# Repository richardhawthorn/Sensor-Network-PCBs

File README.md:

# PCBs for a wireless sensor network

- Arduino based
- 3.3V operation
- RMF12B/RFM69W communication

### License

This work is licensed under a Creative Commons Attribution-ShareAlike 4.0 International License.

<br />
Designed by <a xmlns:cc="http://creativecommons.org/ns#" href="http://www.richardhawthorn.com" property="cc:attributionName" rel="cc:attributionURL" target="_blank">Richard Hawthorn</a><br />
<a rel="license" href="http://creativecommons.org/licenses/by-sa/4.0/" target="_blank">View License</a>

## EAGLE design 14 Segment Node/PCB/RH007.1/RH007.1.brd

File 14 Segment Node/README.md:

### Description

14 Segment LED display, powered by Arduino, with a built in RF radio tranceiver.  
The board can be populated as a full Arduino, or as a shield by populating the 14 segment LEDs + driver.

### Features

- 0.54" 14 segment display, 4 character
- HT16K33 i2c LED driver
- ATMEGA328P with Arduino boot-loader
- RMF12B/RFM69W radio
- 3.3V operation
- Mini USB power connector
- FTDI programming port
- ICSP port
- LED output

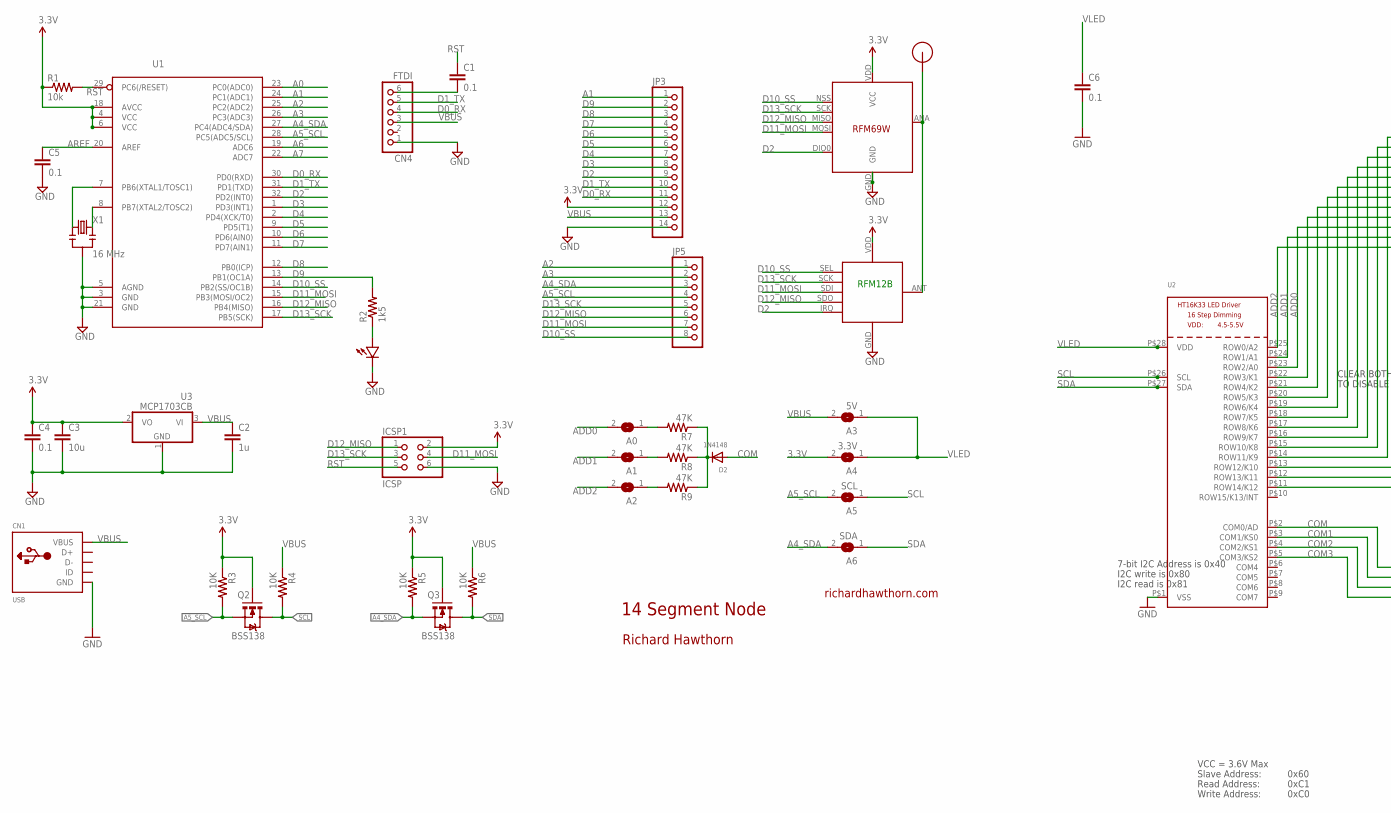
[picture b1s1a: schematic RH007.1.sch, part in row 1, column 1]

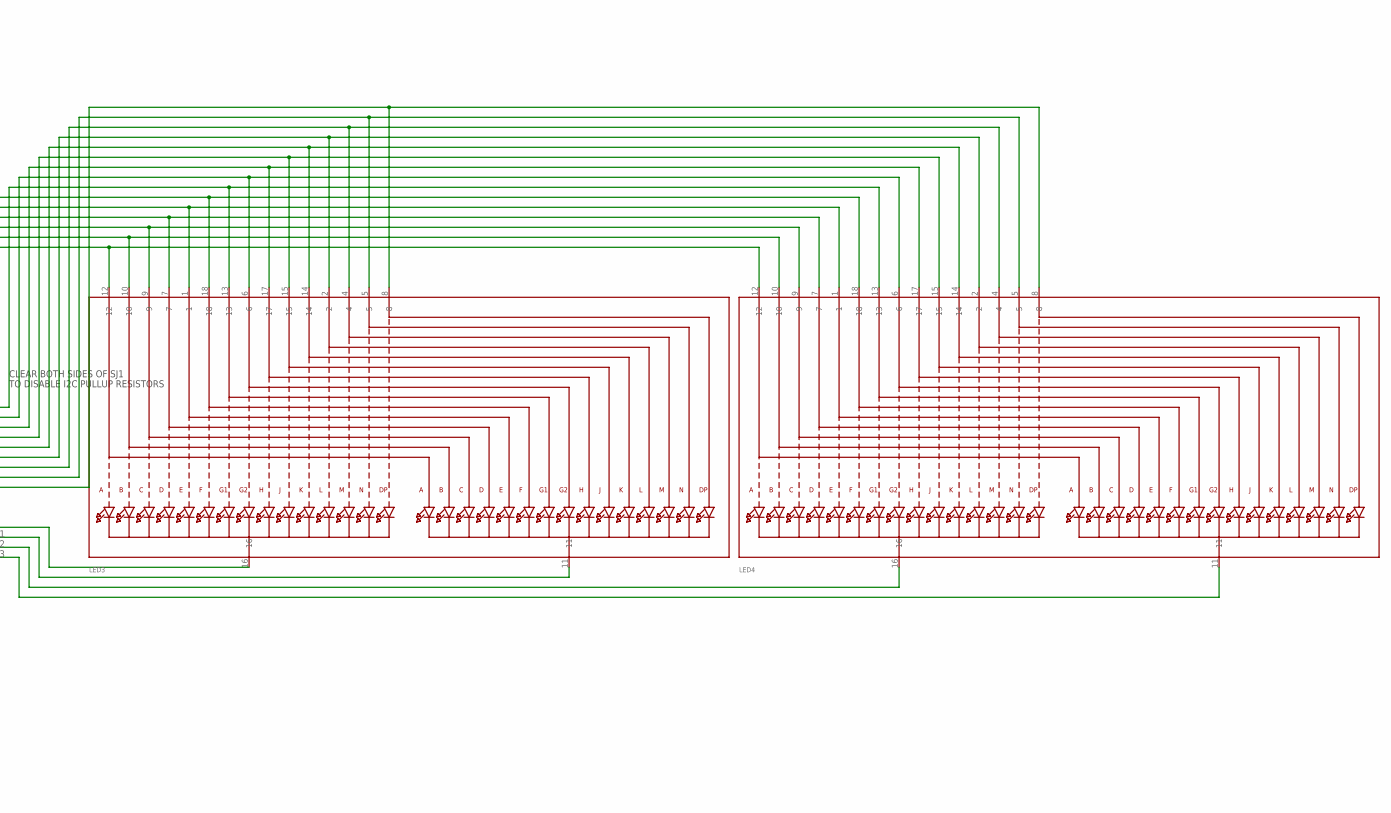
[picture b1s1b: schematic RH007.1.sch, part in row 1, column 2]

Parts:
A0, A1, A2: SOLDERJUMPERREFLOW_NOPASTE; SOLDERJUMPER_REFLOW_NOPASTE
A3: 5V; SOLDERJUMPER_REFLOW_NOPASTE
A4: 3.3V; SOLDERJUMPER_REFLOW_NOPASTE
A5: SCL; SOLDERJUMPER_REFLOW_NOPASTE
A6: SDA; SOLDERJUMPER_REFLOW_NOPASTE
C1, C4, C5, C6: 0.1; 0603-CAP
C2: 1u; 0603-CAP
C3: 10u; 0805-CAP
CN1: USB; USB-MINIB
CN4: FTDI; 1X06
D2: 1N4148; SOD-323F
ICSP1: ICSP; 2X03
JP3: PINHD-1X14; 1X14
JP5: PINHD-1X8; 1X08
LED1: LED0603; 0603-LED
LED3, LED4: DISP_SEGMENT_STARBURST_DUAL_COMMONCATHODE; SEGMENT_STARTBUST_DUAL_KWA-541CBB
Q2, Q3: BSS138; SOT23-3
R1: 10k; 0603-RES
R2: 1k5; 0805
R3, R4, R5, R6: 10K; 0603-RES
R7, R8, R9: 47K; R0805
RF1: RFM12B; RFM12B-MINPADS
RF2: RFM69; RFM69W-MINPADS
U1: ATMega-328; TQFP32-08
U2: HT16K33_SOP28; SOP28_300MIL
U3: MCP1703CB; SOT23
U$1: RFM12B_ANTENNA; RFM12B-ANTENNA
X1: 16 MHz; RESONATOR-SMD

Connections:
3.3V: A4.2, C3.1, C4.1, ICSP1.2, JP3.12, Q2.1 (G), Q3.1 (G), R1.1, R3.1, R5.1, RF1.VDD, RF2.VDD (VCC), U1.4 (VCC), U1.6 (VCC), U1.18 (AVCC), U3.2 (VO)
A0: U1.23 (PC0(ADC0))
A1: JP3.1, U1.24 (PC1(ADC1))
A2: JP5.1, U1.25 (PC2(ADC2))
A3: JP5.2, U1.26 (PC3(ADC3))
A4_SDA: A6.2, JP5.3, Q3.2 (S), R5.2, U1.27 (PC4(ADC4/SDA))
A5_SCL: A5.2, JP5.4, Q2.2 (S), R3.2, U1.28 (PC5(ADC5/SCL))
A6: U1.19 (ADC6)
A7: U1.22 (ADC7)
ADD0: A0.2, LED3.9, LED4.9, U2.P$23 (ROW2/A0)
ADD1: A1.2, LED3.10, LED4.10, U2.P$24 (ROW1/A1)
ADD2: A2.2, LED3.12, LED4.12, U2.P$25 (ROW0/A2)
AREF: C5.1, U1.20 (AREF)
COM: D2.A, LED3.16, U2.P$2 (COM0/AD)
COM1: LED3.11, U2.P$3 (COM1/KS0)
COM2: LED4.16, U2.P$4 (COM2/KS1)
COM3: LED4.11, U2.P$5 (COM3/KS2)
D0_RX: CN4.4, JP3.11, U1.30 (PD0(RXD))
D1_TX: CN4.5, JP3.10, U1.31 (PD1(TXD))
D2: JP3.9, RF1.IRQ, RF2.DIO0, U1.32 (PD2(INT0))
D3: JP3.8, U1.1 (PD3(INT1))
D4: JP3.7, U1.2 (PD4(XCK/T0))
D5: JP3.6, U1.9 (PD5(T1))
D6: JP3.5, U1.10 (PD6(AIN0))
D7: JP3.4, U1.11 (PD7(AIN1))
D8: JP3.3, U1.12 (PB0(ICP))
D9: JP3.2, R2.2, U1.13 (PB1(OC1A))
D10_SS: JP5.8, RF1.SEL, RF2.NSS (SEL), U1.14 (PB2(SS/OC1B))
D11_MOSI: ICSP1.4, JP5.7, RF1.SDI (SDI/MOSI), RF2.MOSI, U1.15 (PB3(MOSI/OC2))
D12_MISO: ICSP1.1, JP5.6, RF1.SDO (SDO/MISO), RF2.MISO, U1.16 (PB4(MISO))
D13_SCK: ICSP1.3, JP5.5, RF1.SCK, RF2.SCK, U1.17 (PB5(SCK))
GND: C2.2, C3.2, C4.2, C5.2, C6.2, CN1.GND, CN4.1, ICSP1.6, JP3.14, LED1.MINUS, RF1.GND, RF2.GND, U1.3 (GND), U1.5 (AGND), U1.21 (GND), U2.P$1 (VSS), U3.1 (GND), X1.2
unnamed: U1.7 (PB6(XTAL1/TOSC1)), X1.1
unnamed: LED1.PLUS, R2.1
unnamed: RF1.ANT, RF2.ANA (ANT), U$1.P$1
unnamed: A0.1, R7.2
unnamed: D2.C, R7.1, R8.1, R9.1
unnamed: A2.1, R9.2
unnamed: A1.1, R8.2
unnamed: C1.2, CN4.6
unnamed: U1.8 (PB7(XTAL2/TOSC2)), X1.3
unnamed: LED3.7, LED4.7, U2.P$22 (ROW3/K1)
unnamed: LED3.1, LED4.1, U2.P$21 (ROW4/K2)
unnamed: LED3.18, LED4.18, U2.P$20 (ROW5/K3)
unnamed: LED3.13, LED4.13, U2.P$19 (ROW6/K4)
unnamed: LED3.6, LED4.6, U2.P$18 (ROW7/K5)
unnamed: LED3.17, LED4.17, U2.P$17 (ROW8/K6)
unnamed: LED3.15, LED4.15, U2.P$16 (ROW9/K7)
unnamed: LED3.14, LED4.14, U2.P$15 (ROW10/K8)
unnamed: LED3.2, LED4.2, U2.P$14 (ROW11/K9)
unnamed: LED3.4, LED4.4, U2.P$13 (ROW12/K10)
unnamed: LED3.5, LED4.5, U2.P$12 (ROW13/K11)
unnamed: LED3.8, LED4.8, U2.P$11 (ROW14/K12)
RST: C1.1, ICSP1.5, R1.2, U1.29 (PC6(/RESET))
SCL: A5.1, Q2.3 (D), R4.2, U2.P$26 (SCL)
SDA: A6.1, Q3.3 (D), R6.2, U2.P$27 (SDA)
VBUS: A3.2, C2.1, CN1.VBUS, CN4.3, JP3.13, R4.1, R6.1, U3.3 (VI)
VLED: A3.1, A4.1, C6.1, U2.P$28 (VDD)

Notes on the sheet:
14 Segment Node
richardhawthorn.com
Richard Hawthorn
RFM12B
CLEAR BOTH SIDES OF SJ1
TO DISABLE I2C PULLUP RESISTORS
7-bit I2C Address is 0x40
I2C write is 0x80
I2C read is 0x81
VCC = 3.6V Max
Read Address:
Write Address:
Slave Address:
0x60
0xC1
0xC0

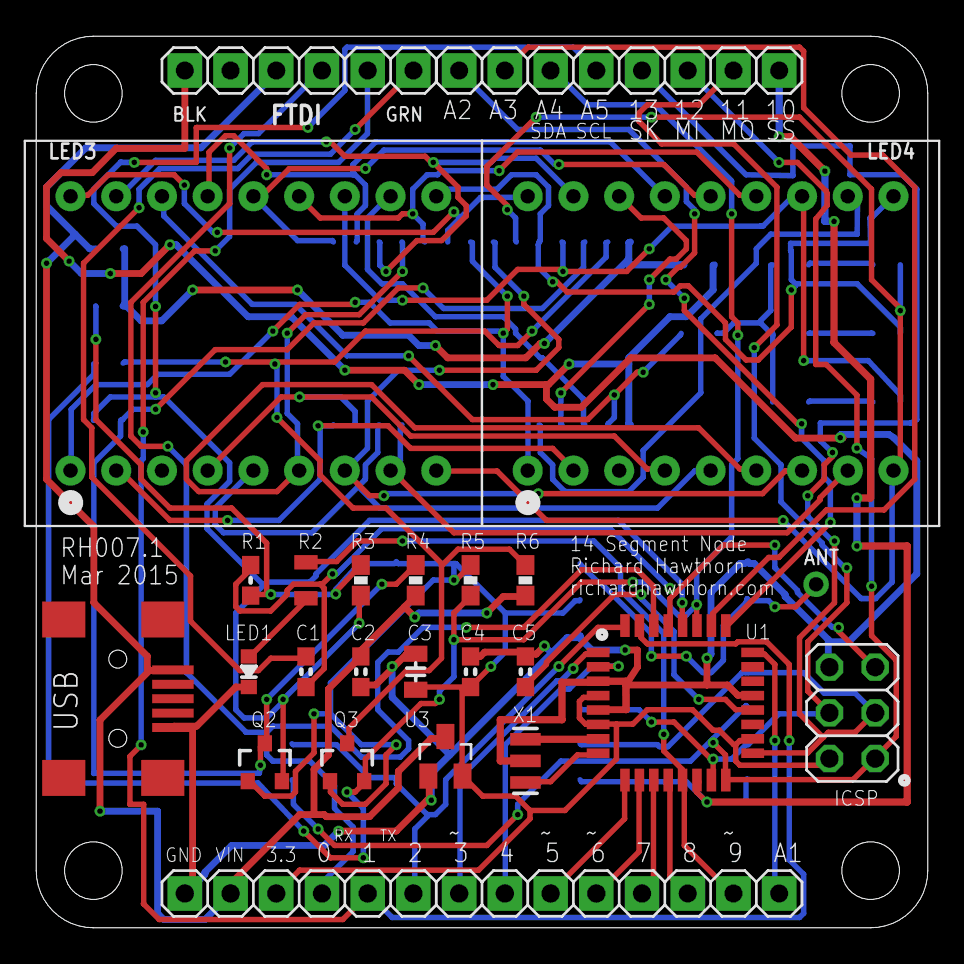
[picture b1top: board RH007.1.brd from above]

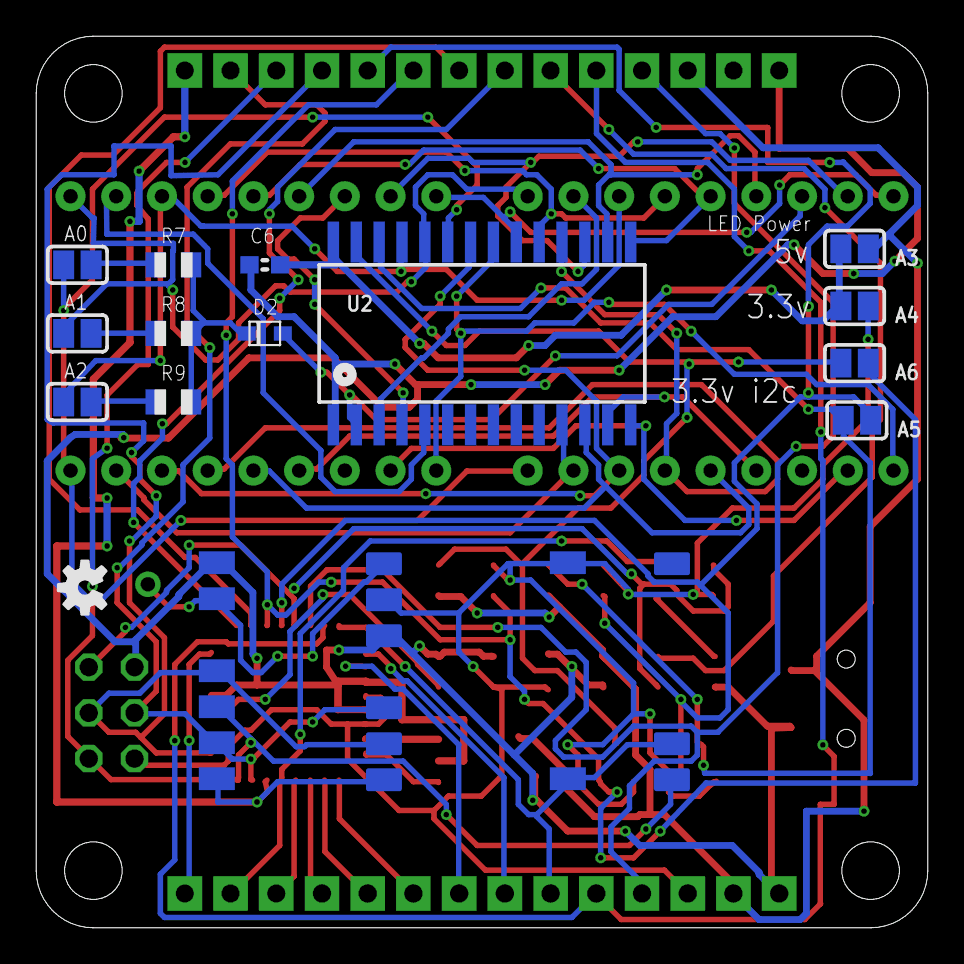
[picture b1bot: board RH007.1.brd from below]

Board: 2 copper layers, 49.5 x 49.5 mm, 41 parts (16 on the bottom side), 55 nets.

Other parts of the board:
U$3: OSHW-LOGO-S

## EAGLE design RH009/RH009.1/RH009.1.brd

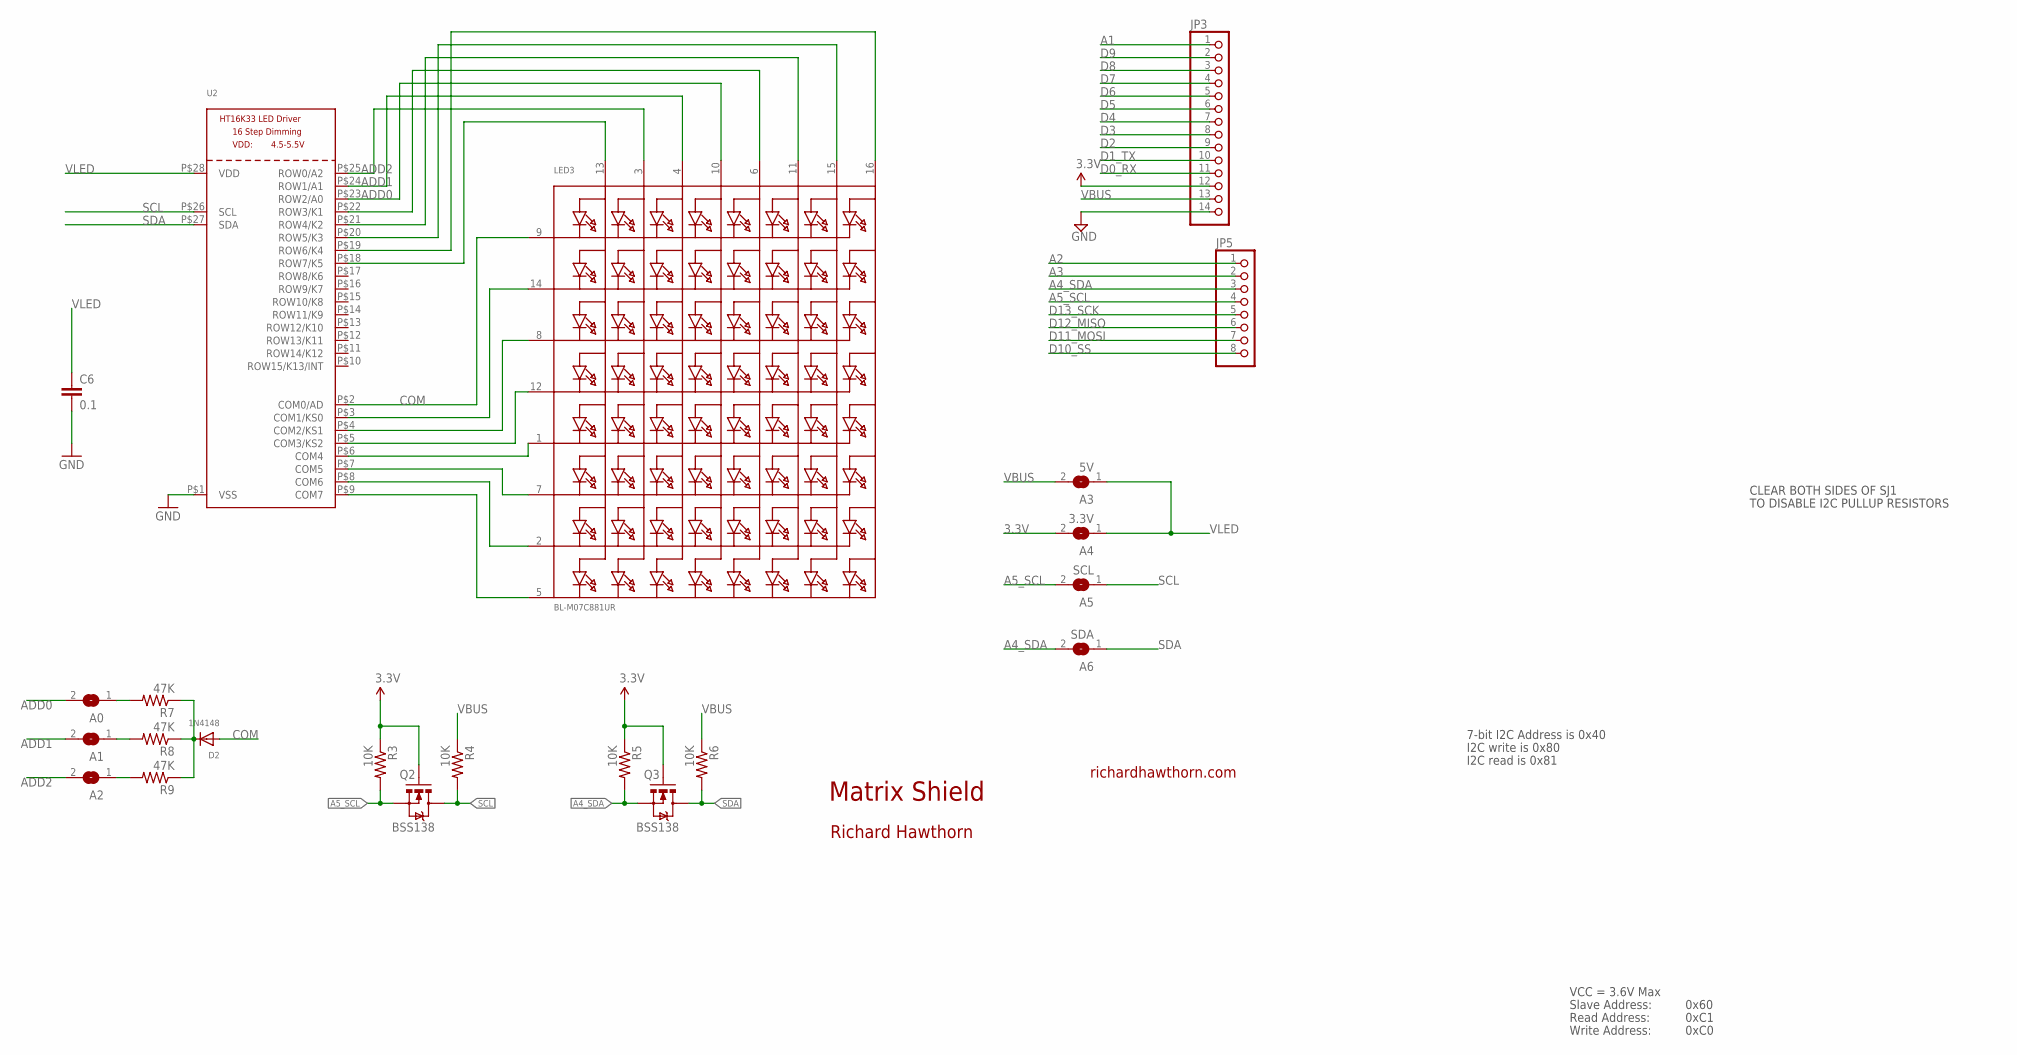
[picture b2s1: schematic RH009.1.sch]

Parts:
A0, A1, A2: SOLDERJUMPERREFLOW_NOPASTE; SOLDERJUMPER_REFLOW_NOPASTE
A3: 5V; SOLDERJUMPER_REFLOW_NOPASTE
A4: 3.3V; SOLDERJUMPER_REFLOW_NOPASTE
A5: SCL; SOLDERJUMPER_REFLOW_NOPASTE
A6: SDA; SOLDERJUMPER_REFLOW_NOPASTE
C6: 0.1; 0603-CAP
D2: 1N4148; SOD-323F
JP3: PINHD-1X14; 1X14
JP5: PINHD-1X8; 1X08
LED3: BL-M07C881UR; SEGMENT_BL-M12A881UR
Q2, Q3: BSS138; SOT23-3
R3, R4, R5, R6: 10K; 0603-RES
R7, R8, R9: 47K; R0805
U2: HT16K33_SOP28; SOP28_300MIL

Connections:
3.3V: A4.2, JP3.12, Q2.1 (G), Q3.1 (G), R3.1, R5.1
A1: JP3.1
A2: JP5.1
A3: JP5.2
A4_SDA: A6.2, JP5.3, Q3.2 (S), R5.2
A5_SCL: A5.2, JP5.4, Q2.2 (S), R3.2
ADD0: A0.2, LED3.10 (A4), U2.P$23 (ROW2/A0)
ADD1: A1.2, LED3.4 (A3), U2.P$24 (ROW1/A1)
ADD2: A2.2, LED3.3 (A2), U2.P$25 (ROW0/A2)
COM: D2.A, LED3.9 (K1), U2.P$2 (COM0/AD)
D0_RX: JP3.11
D1_TX: JP3.10
D2: JP3.9
D3: JP3.8
D4: JP3.7
D5: JP3.6
D6: JP3.5
D7: JP3.4
D8: JP3.3
D9: JP3.2
D10_SS: JP5.8
D11_MOSI: JP5.7
D12_MISO: JP5.6
D13_SCK: JP5.5
GND: C6.2, JP3.14, U2.P$1 (VSS)
unnamed: LED3.5 (K8), U2.P$9 (COM7)
unnamed: A0.1, R7.2
unnamed: LED3.2 (K7), U2.P$8 (COM6)
unnamed: LED3.7 (K6), U2.P$7 (COM5)
unnamed: D2.C, R7.1, R8.1, R9.1
unnamed: A2.1, R9.2
unnamed: A1.1, R8.2
unnamed: LED3.1 (K5), U2.P$6 (COM4)
unnamed: LED3.12 (K4), U2.P$5 (COM3/KS2)
unnamed: LED3.8 (K3), U2.P$4 (COM2/KS1)
unnamed: LED3.14 (K2), U2.P$3 (COM1/KS0)
unnamed: LED3.6 (A5), U2.P$22 (ROW3/K1)
unnamed: LED3.11 (A6), U2.P$21 (ROW4/K2)
unnamed: LED3.13 (A1), U2.P$18 (ROW7/K5)
SCL: A5.1, Q2.3 (D), R4.2, U2.P$26 (SCL)
SDA: A6.1, Q3.3 (D), R6.2, U2.P$27 (SDA)
SEG_F: LED3.15 (A7), U2.P$20 (ROW5/K3)
SEG_G: LED3.16 (A8), U2.P$19 (ROW6/K4)
VBUS: A3.2, JP3.13, R4.1, R6.1
VLED: A3.1, A4.1, C6.1, U2.P$28 (VDD)

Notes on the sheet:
Matrix Shield
richardhawthorn.com
Richard Hawthorn
CLEAR BOTH SIDES OF SJ1
TO DISABLE I2C PULLUP RESISTORS
7-bit I2C Address is 0x40
I2C write is 0x80
I2C read is 0x81
VCC = 3.6V Max
Read Address:
Write Address:
Slave Address:
0x60
0xC1
0xC0

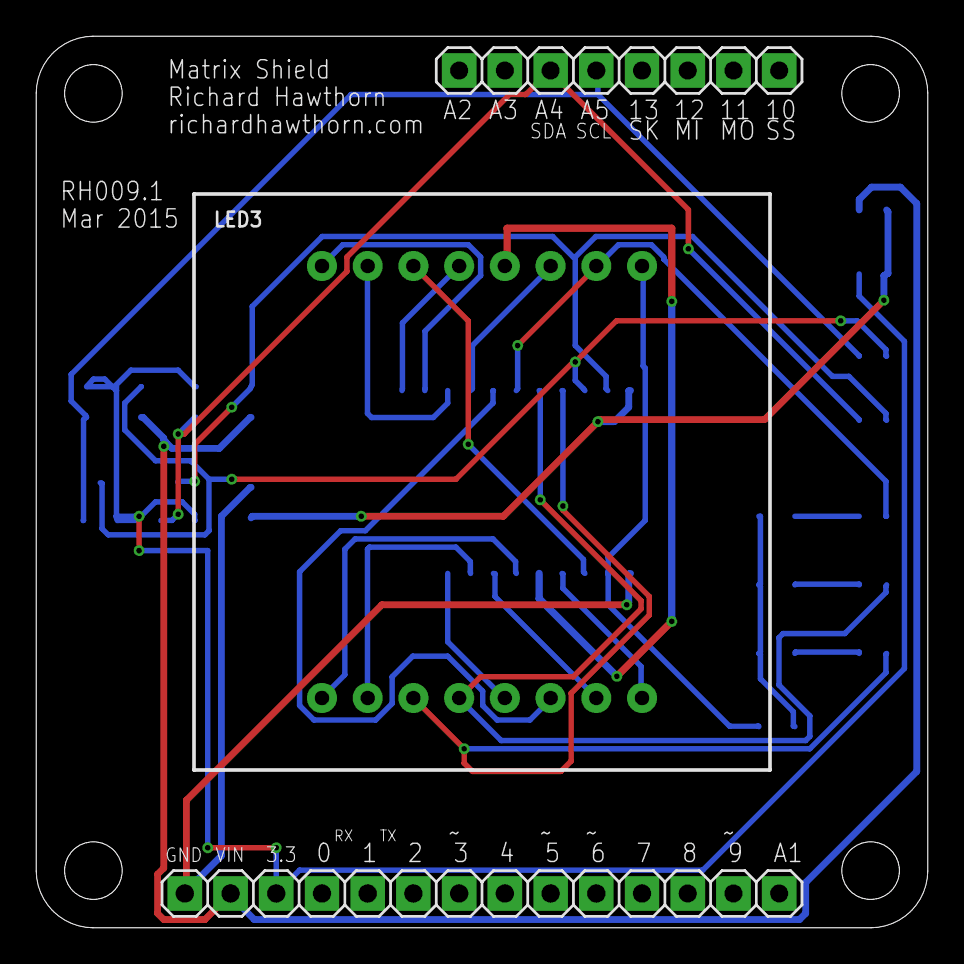
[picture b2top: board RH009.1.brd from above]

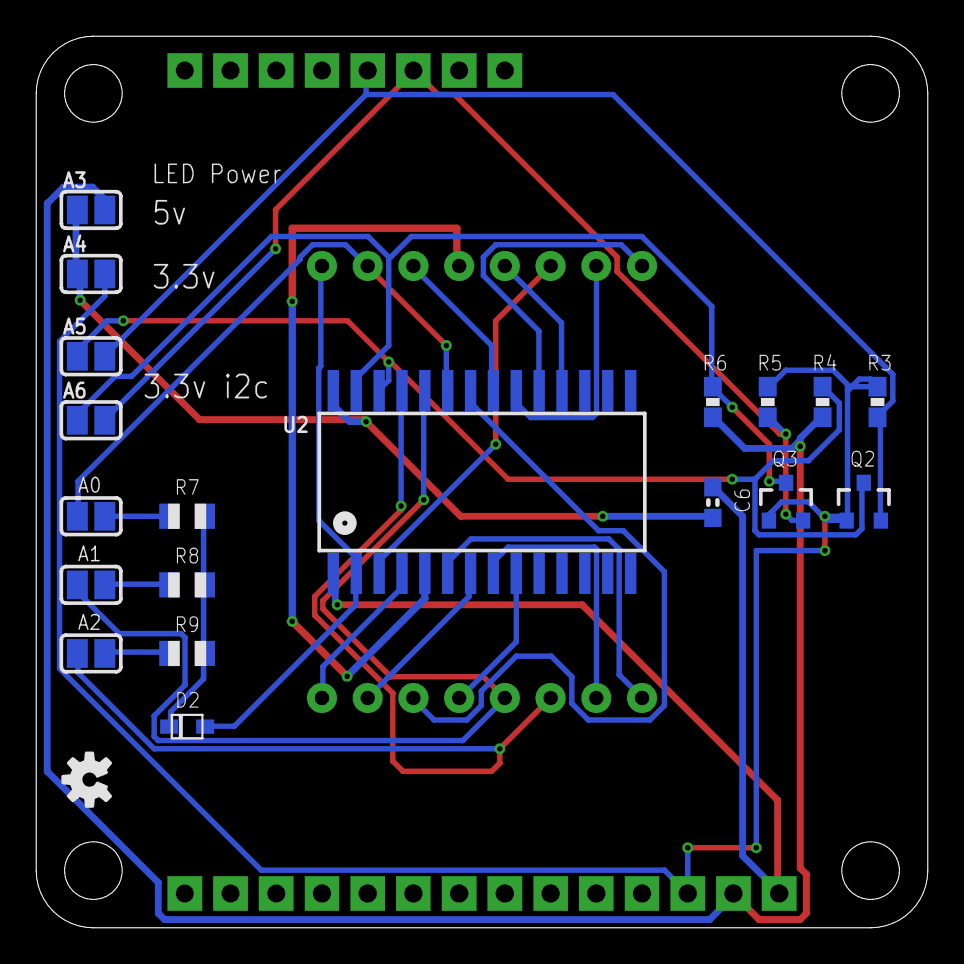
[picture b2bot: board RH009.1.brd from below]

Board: 2 copper layers, 49.5 x 49.5 mm, 23 parts (20 on the bottom side), 28 nets.

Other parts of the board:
U$3: OSHW-LOGO-S

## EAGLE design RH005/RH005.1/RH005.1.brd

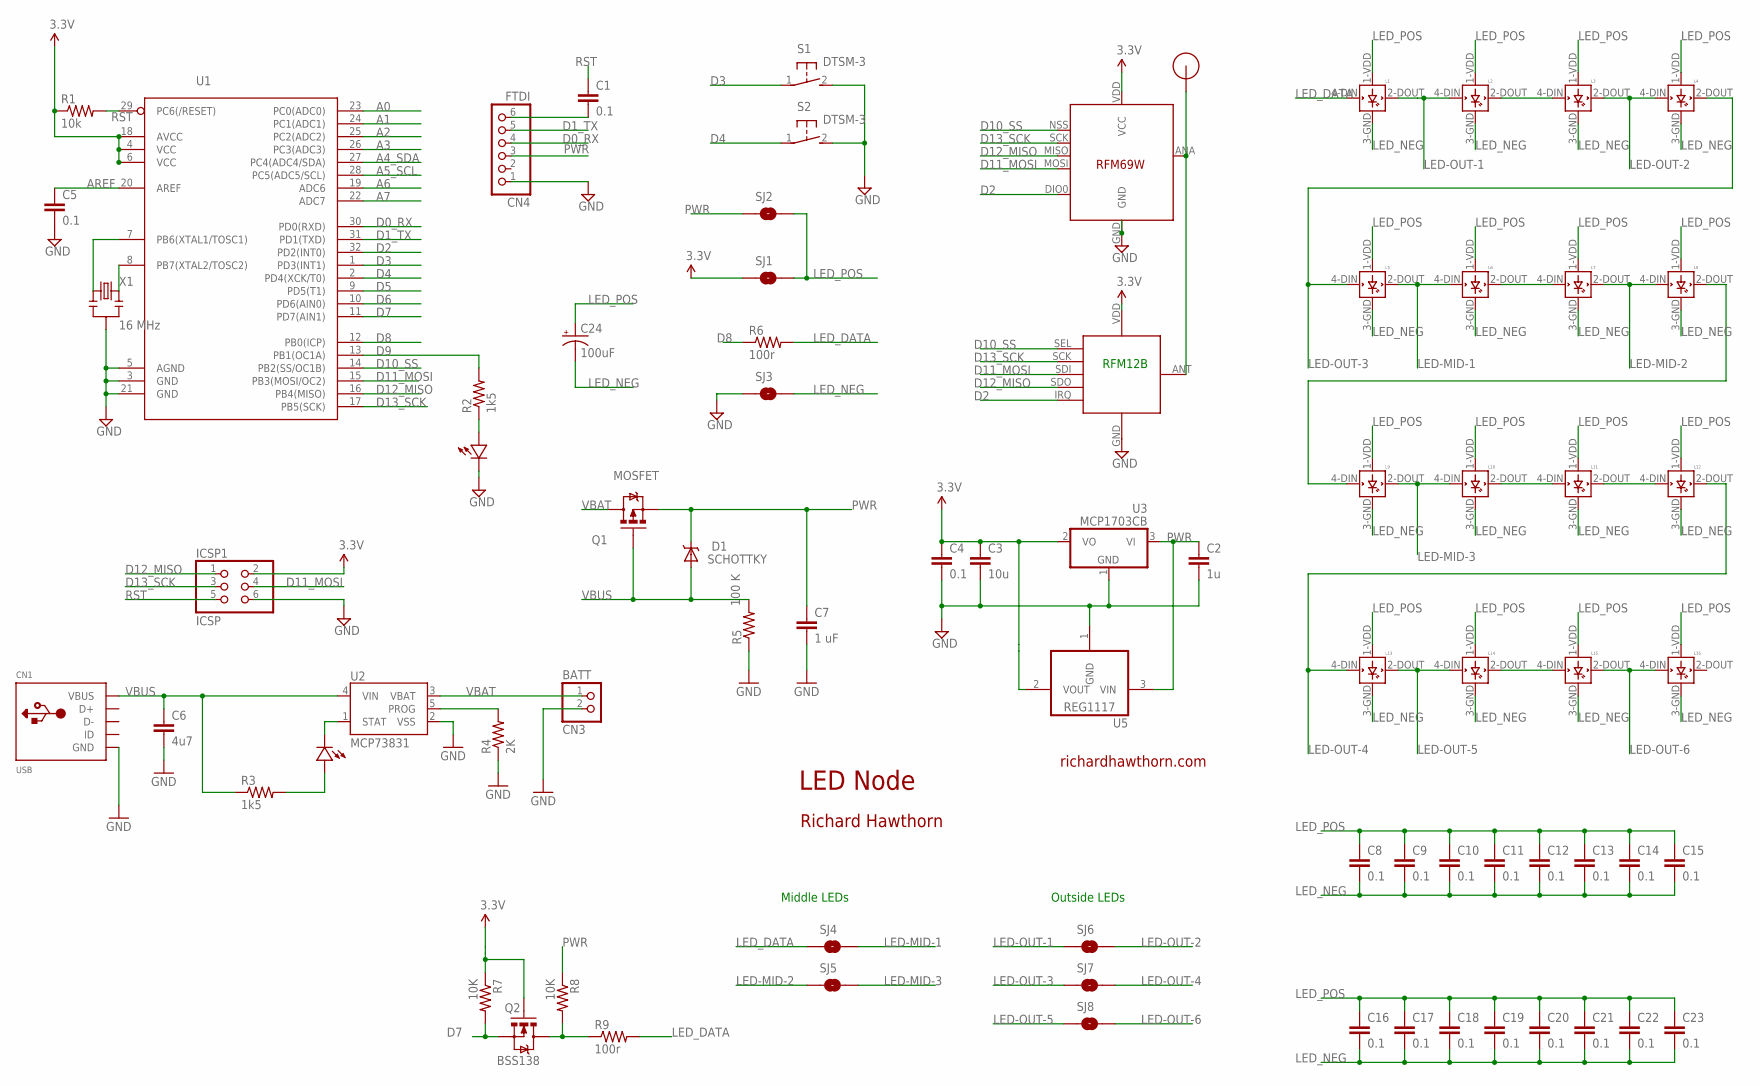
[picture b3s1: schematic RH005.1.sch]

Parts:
C1, C4, C5, C8, C9, C10, C11, C12, C13, C14, C15, C16, C17, C18, C19, C20, C21, C22, C23: 0.1; 0603-CAP
C2: 1u; 0603-CAP
C3: 10u; 0805-CAP
C6: 4u7; 0603-CAP
C7: 1 uF; 0805
C24: 100uF; EIA7343
CN1: USB; USB-MINIB
CN3: BATT; JST-PH-2-SMT-RA
CN4: FTDI; 1X06
D1: SCHOTTKY; SMA-DIODE
ICSP1: ICSP; 2X03
L1, L2, L3, L4, L5, L6, L7, L8, L9, L10, L11, L12, L13, L14, L15, L16: WS2812B
LED1, LED2: LED0603; 0603-LED
Q1: MOSFET; SOT23-3
Q2: BSS138; SOT23-3
R1: 10k; 0603-RES
R2, R3: 1k5; 0603-RES
R4: 2K; 0603-RES
R5: 100 K; 0805
R6, R9: 100r; 0603-RES
R7, R8: 10K; 0805
RF1: RFM12B; RFM12B-MINPADS
RF2: RFM69; RFM69W-MINPADS
S1, S2: DTSM-3
SJ1, SJ2, SJ3: SOLDERJUMPERNO; SJ_2S-NO
SJ4, SJ5, SJ6, SJ7, SJ8: JUMPER-PAD-2-NOYES_SILK; PAD-JUMPER-2-NO_YES_SILK
U1: ATMega-328; TQFP32-08
U2: MCP73831; SOT23-5
U3: MCP1703CB; SOT23
U5: REG1117; SOT223
U$1: RFM12B_ANTENNA; RFM12B-ANTENNA
X1: 16 MHz; RESONATOR-SMD

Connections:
A0: U1.23 (PC0(ADC0))
A1: U1.24 (PC1(ADC1))
A2: U1.25 (PC2(ADC2))
A3: U1.26 (PC3(ADC3))
A4_SDA: U1.27 (PC4(ADC4/SDA))
A5_SCL: U1.28 (PC5(ADC5/SCL))
A6: U1.19 (ADC6)
A7: U1.22 (ADC7)
AREF: C5.1, U1.20 (AREF)
D0_RX: CN4.4, U1.30 (PD0(RXD))
D1_TX: CN4.5, U1.31 (PD1(TXD))
D2: RF1.IRQ, RF2.DIO0, U1.32 (PD2(INT0))
D3: S1.1, U1.1 (PD3(INT1))
D4: S2.1, U1.2 (PD4(XCK/T0))
D5: U1.9 (PD5(T1))
D6: U1.10 (PD6(AIN0))
D7: Q2.2 (S), R7.2, U1.11 (PD7(AIN1))
D8: R6.1, U1.12 (PB0(ICP))
D9: R2.2, U1.13 (PB1(OC1A))
D10_SS: RF1.SEL, RF2.NSS (SEL), U1.14 (PB2(SS/OC1B))
D11_MOSI: ICSP1.4, RF1.SDI (SDI/MOSI), RF2.MOSI, U1.15 (PB3(MOSI/OC2))
D12_MISO: ICSP1.1, RF1.SDO (SDO/MISO), RF2.MISO, U1.16 (PB4(MISO))
D13_SCK: ICSP1.3, RF1.SCK, RF2.SCK, U1.17 (PB5(SCK))
GND: C2.2, C3.2, C4.2, C5.2, C6.2, C7.2, CN1.GND, CN3.2 (1), CN4.1, ICSP1.6, LED2.MINUS, R4.1, R5.1, RF1.GND, RF2.GND, S1.2, S2.2, SJ3.1, U1.3 (GND), U1.5 (AGND), U1.21 (GND), U2.2 (VSS), U3.1 (GND), U5.1 (GND), X1.2
HV_LED: Q2.3 (D), R8.2, R9.1
LED-MID-1: L5.2-DOUT (DOUT), L6.4-DIN (DIN), SJ4.2
LED-MID-2: L7.2-DOUT (DOUT), L8.4-DIN (DIN), SJ5.1
LED-MID-3: L9.2-DOUT (DOUT), L10.4-DIN (DIN), SJ5.2
LED-OUT-1: L1.2-DOUT (DOUT), L2.4-DIN (DIN), SJ6.1
LED-OUT-2: L3.2-DOUT (DOUT), L4.4-DIN (DIN), SJ6.2
LED-OUT-3: L4.2-DOUT (DOUT), L5.4-DIN (DIN), SJ7.1
LED-OUT-4: L12.2-DOUT (DOUT), L13.4-DIN (DIN), SJ7.2
LED-OUT-5: L13.2-DOUT (DOUT), L14.4-DIN (DIN), SJ8.1
LED-OUT-6: L15.2-DOUT (DOUT), L16.4-DIN (DIN), SJ8.2
LED_DATA: L1.4-DIN (DIN), R6.2, R9.2, SJ4.1
LED_NEG: C8.2, C9.2, C10.2, C11.2, C12.2, C13.2, C14.2, C15.2, C16.2, C17.2, C18.2, C19.2, C20.2, C21.2, C22.2, C23.2, C24.C (-), L1.3-GND (GND), L2.3-GND (GND), L3.3-GND (GND), L4.3-GND (GND), L5.3-GND (GND), L6.3-GND (GND), L7.3-GND (GND), L8.3-GND (GND), L9.3-GND (GND), L10.3-GND (GND), L11.3-GND (GND), L12.3-GND (GND), L13.3-GND (GND), L14.3-GND (GND), L15.3-GND (GND), L16.3-GND (GND), SJ3.2
LED_POS: C8.1, C9.1, C10.1, C11.1, C12.1, C13.1, C14.1, C15.1, C16.1, C17.1, C18.1, C19.1, C20.1, C21.1, C22.1, C23.1, C24.A (+), L1.1-VDD (VDD), L2.1-VDD (VDD), L3.1-VDD (VDD), L4.1-VDD (VDD), L5.1-VDD (VDD), L6.1-VDD (VDD), L7.1-VDD (VDD), L8.1-VDD (VDD), L9.1-VDD (VDD), L10.1-VDD (VDD), L11.1-VDD (VDD), L12.1-VDD (VDD), L13.1-VDD (VDD), L14.1-VDD (VDD), L15.1-VDD (VDD), L16.1-VDD (VDD), SJ1.2, SJ2.2
unnamed: U1.7 (PB6(XTAL1/TOSC1)), X1.1
unnamed: LED2.PLUS, R2.1
unnamed: RF1.ANT, RF2.ANA (ANT), U$1.P$1
unnamed: LED1.PLUS, R3.2
unnamed: L2.2-DOUT (DOUT), L3.4-DIN (DIN)
unnamed: L6.2-DOUT (DOUT), L7.4-DIN (DIN)
unnamed: L8.2-DOUT (DOUT), L9.4-DIN (DIN)
unnamed: L10.2-DOUT (DOUT), L11.4-DIN (DIN)
unnamed: L11.2-DOUT (DOUT), L12.4-DIN (DIN)
unnamed: L14.2-DOUT (DOUT), L15.4-DIN (DIN)
unnamed: C1.2, CN4.6
unnamed: U1.8 (PB7(XTAL2/TOSC2)), X1.3
PROG: R4.2, U2.5 (PROG)
PWR: C2.1, C7.1, CN4.3, D1.C, Q1.2 (S), R8.1, SJ2.1, U3.3 (VI), U5.3 (VIN)
RST: C1.1, ICSP1.5, R1.2, U1.29 (PC6(/RESET))
STAT: LED1.MINUS, U2.1 (STAT)
VBAT: CN3.1 (2), Q1.3 (D), U2.3 (VBAT)
VBUS: C6.1, CN1.VBUS, D1.A, Q1.1 (G), R3.1, R5.2, U2.4 (VIN)
VCC: C3.1, C4.1, ICSP1.2, Q2.1 (G), R1.1, R7.1, RF1.VDD, RF2.VDD (VCC), SJ1.1, U1.4 (VCC), U1.6 (VCC), U1.18 (AVCC), U3.2 (VO), U5.2 (VOUT)

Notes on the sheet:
LED Node
richardhawthorn.com
Richard Hawthorn
RFM12B
Middle LEDs
Outside LEDs

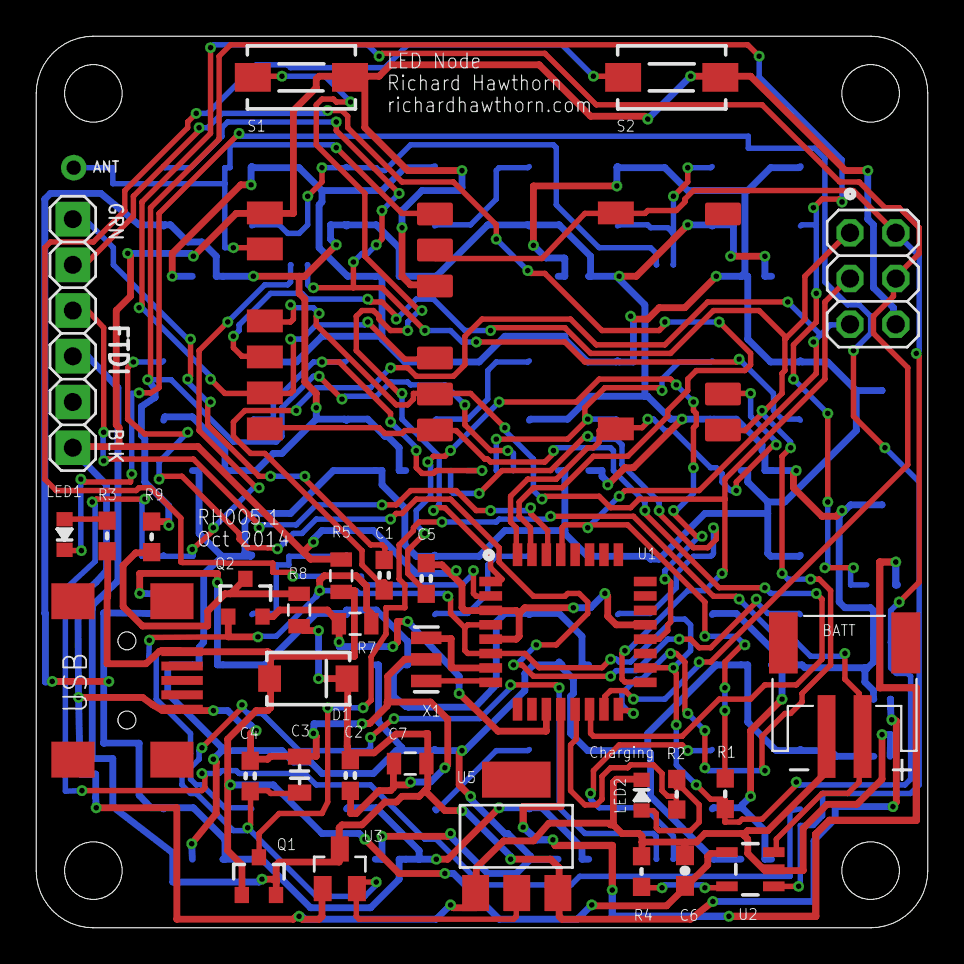
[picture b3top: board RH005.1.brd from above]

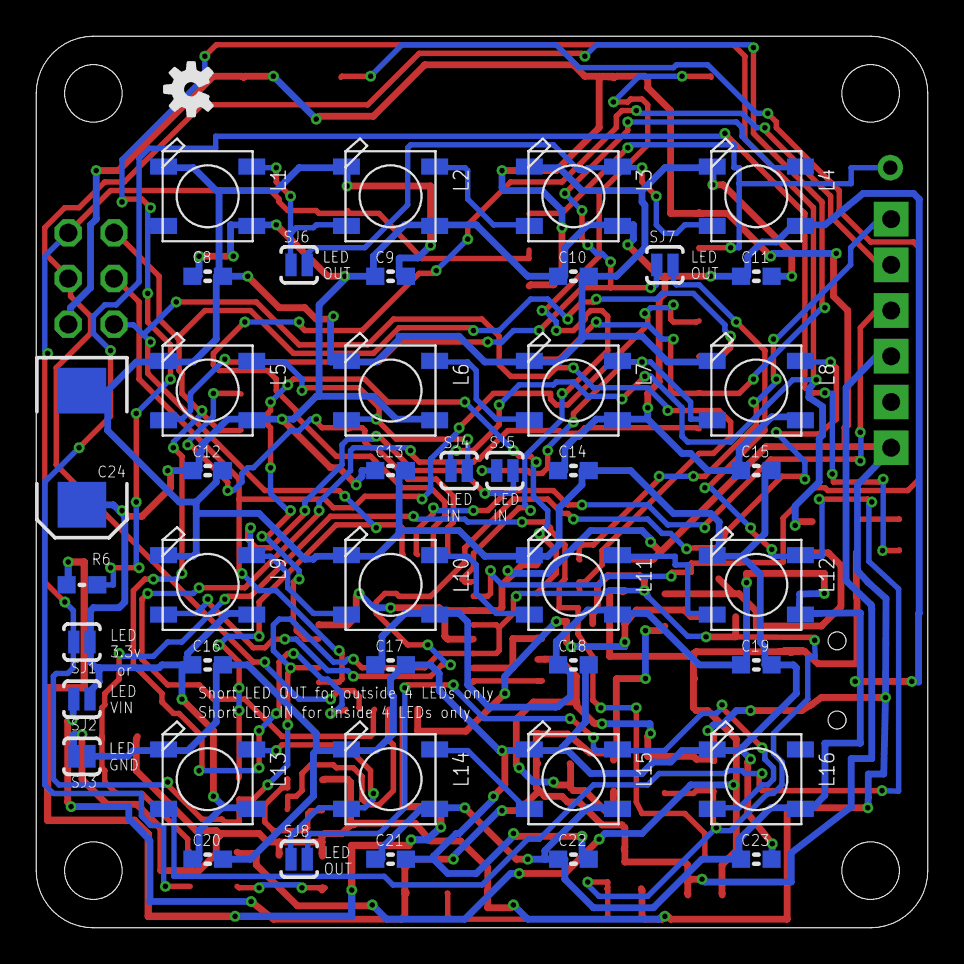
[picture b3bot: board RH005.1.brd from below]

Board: 2 copper layers, 49.5 x 49.5 mm, 77 parts (43 on the bottom side), 46 nets.

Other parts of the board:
U$3: OSHW-LOGO-S

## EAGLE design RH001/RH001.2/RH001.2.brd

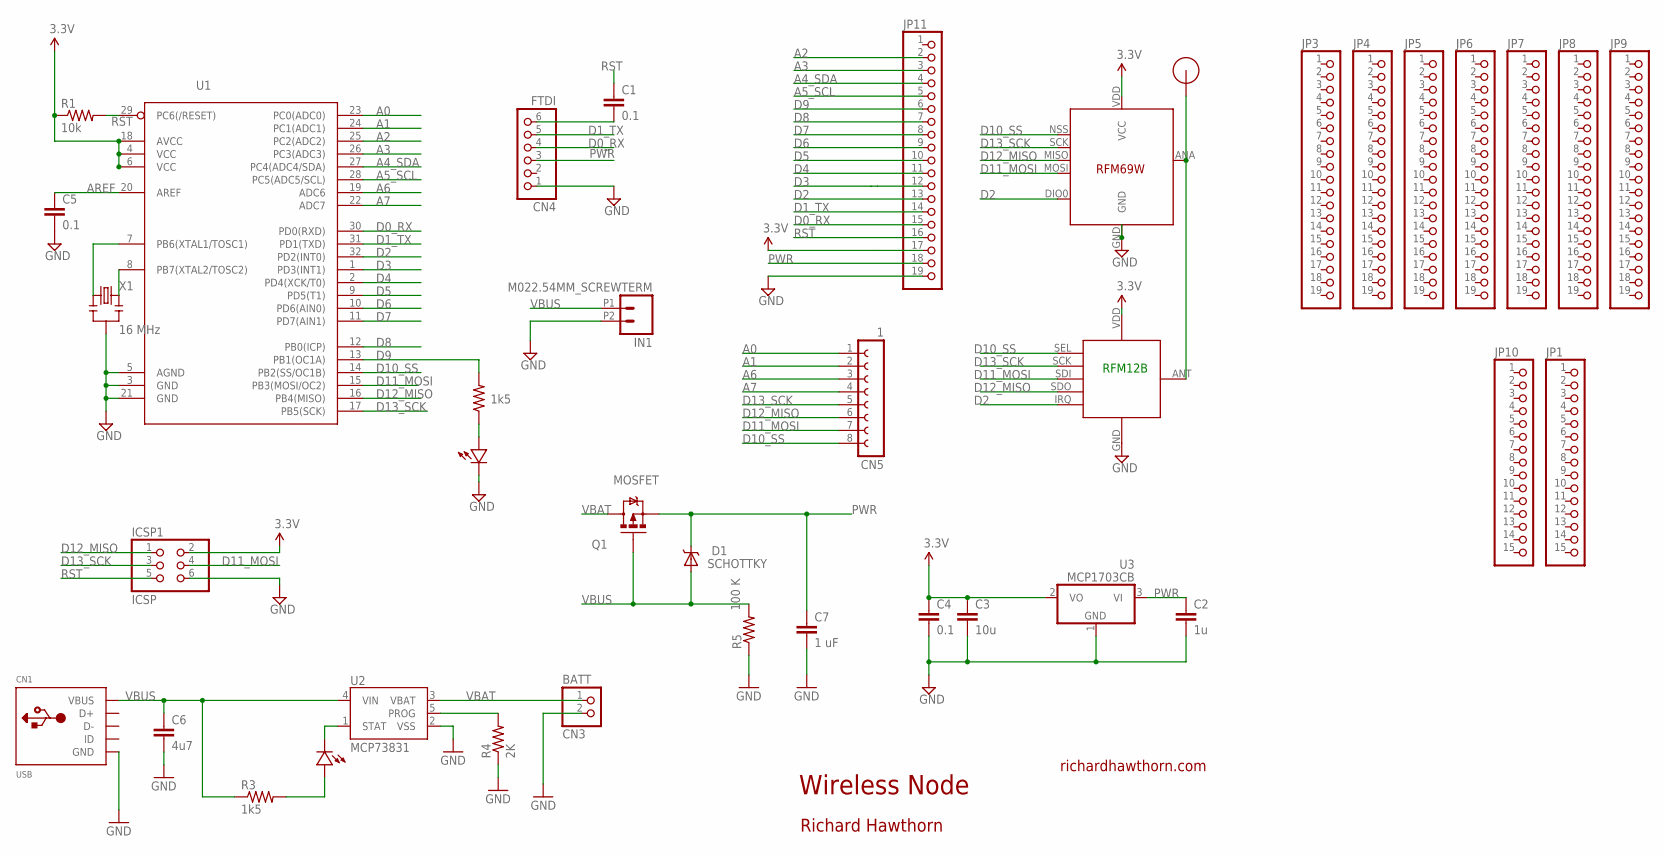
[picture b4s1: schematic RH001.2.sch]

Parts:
C1, C4, C5: 0.1; 0603-CAP
C2: 1u; 0603-CAP
C3: 10u; 0805-CAP
C6: 4u7; 0603-CAP
C7: 1 uF; 0805
CN1: USB; USB-MINIB
CN3: BATT; JST-PH-2-SMT-RA
CN4: FTDI; 1X06
CN5: 1; FE08
D1: SCHOTTKY; SMA-DIODE
ICSP1: ICSP; 2X03
IN1: M022.54MM_SCREWTERM; 1X02_2.54_SCREWTERM
JP1, JP10: PINHD-1X15; 1X15
JP3, JP4, JP5, JP6, JP7, JP8, JP9, JP11: PINHD-1X19; 1X19
LED1, LED2: LED0603; 0603-LED
Q1: MOSFET; SOT23-3
R1: 10k; 0603-RES
R2, R3: 1k5; 0603-RES
R4: 2K; 0603-RES
R5: 100 K; 0805
RF1: RFM12B; RFM12B-MINPADS
RF2: RFM69; RFM69W-MINPADS
U1: ATMega-328; TQFP32-08
U2: MCP73831; SOT23-5
U3: MCP1703CB; SOT23
U$1: RFM12B_ANTENNA; RFM12B-ANTENNA
X1: 16 MHz; RESONATOR-SMD

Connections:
A0: CN5.1, U1.23 (PC0(ADC0))
A1: CN5.2, U1.24 (PC1(ADC1))
A2: JP11.2, U1.25 (PC2(ADC2))
A3: JP11.3, U1.26 (PC3(ADC3))
A4_SDA: JP11.4, U1.27 (PC4(ADC4/SDA))
A5_SCL: JP11.5, U1.28 (PC5(ADC5/SCL))
A6: CN5.3, U1.19 (ADC6)
A7: CN5.4, U1.22 (ADC7)
AREF: C5.1, U1.20 (AREF)
D0_RX: CN4.4, JP11.15, U1.30 (PD0(RXD))
D1_TX: CN4.5, JP11.14, U1.31 (PD1(TXD))
D2: JP11.13, RF1.IRQ, RF2.DIO0, U1.32 (PD2(INT0))
D3: JP11.12, U1.1 (PD3(INT1))
D4: JP11.11, U1.2 (PD4(XCK/T0))
D5: JP11.10, U1.9 (PD5(T1))
D6: JP11.9, U1.10 (PD6(AIN0))
D7: JP11.8, U1.11 (PD7(AIN1))
D8: JP11.7, U1.12 (PB0(ICP))
D9: JP11.6, R2.2, U1.13 (PB1(OC1A))
D10_SS: CN5.8, RF1.SEL, RF2.NSS (SEL), U1.14 (PB2(SS/OC1B))
D11_MOSI: CN5.7, ICSP1.4, RF1.SDI (SDI/MOSI), RF2.MOSI, U1.15 (PB3(MOSI/OC2))
D12_MISO: CN5.6, ICSP1.1, RF1.SDO (SDO/MISO), RF2.MISO, U1.16 (PB4(MISO))
D13_SCK: CN5.5, ICSP1.3, RF1.SCK, RF2.SCK, U1.17 (PB5(SCK))
GND: C2.2, C3.2, C4.2, C5.2, C6.2, C7.2, CN1.GND, CN3.2 (1), CN4.1, ICSP1.6, IN1.P2 (2), JP11.19, LED2.MINUS, R4.1, R5.1, RF1.GND, RF2.GND, U1.3 (GND), U1.5 (AGND), U1.21 (GND), U2.2 (VSS), U3.1 (GND), X1.2
unnamed: U1.7 (PB6(XTAL1/TOSC1)), X1.1
unnamed: LED2.PLUS, R2.1
unnamed: RF1.ANT, RF2.ANA (ANT), U$1.P$1
unnamed: LED1.PLUS, R3.2
unnamed: C1.2, CN4.6
unnamed: U1.8 (PB7(XTAL2/TOSC2)), X1.3
PROG: R4.2, U2.5 (PROG)
PWR: C2.1, C7.1, CN4.3, D1.C, JP11.18, Q1.2 (S), U3.3 (VI)
RST: C1.1, ICSP1.5, JP11.16, R1.2, U1.29 (PC6(/RESET))
STAT: LED1.MINUS, U2.1 (STAT)
VBAT: CN3.1 (2), Q1.3 (D), U2.3 (VBAT)
VBUS: C6.1, CN1.VBUS, D1.A, IN1.P1 (1), Q1.1 (G), R3.1, R5.2, U2.4 (VIN)
VCC: C3.1, C4.1, ICSP1.2, JP11.17, R1.1, RF1.VDD, RF2.VDD (VCC), U1.4 (VCC), U1.6 (VCC), U1.18 (AVCC), U3.2 (VO)

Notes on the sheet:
Wireless Node
richardhawthorn.com
Richard Hawthorn
RFM12B

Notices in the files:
parts and their libraries:
SparkFun-Aesthetics: Licensing: CC v3.0 Share-Alike You are welcome to use this library for commercial purposes.
SparkFun-Retired: Licensing:Creative Commons ShareAlike 4.0 International - https://creativecommons.org/licenses/by-sa/4.0
